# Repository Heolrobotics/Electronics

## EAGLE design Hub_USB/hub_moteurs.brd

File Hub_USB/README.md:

# Hub USB

 **This work is licensed under a [Creative Commons Attribution-ShareAlike 4.0 International License](http://creativecommons.org/licenses/by-sa/4.0/).**

**Authors:** Alexandre Le Falher, Nicolas.

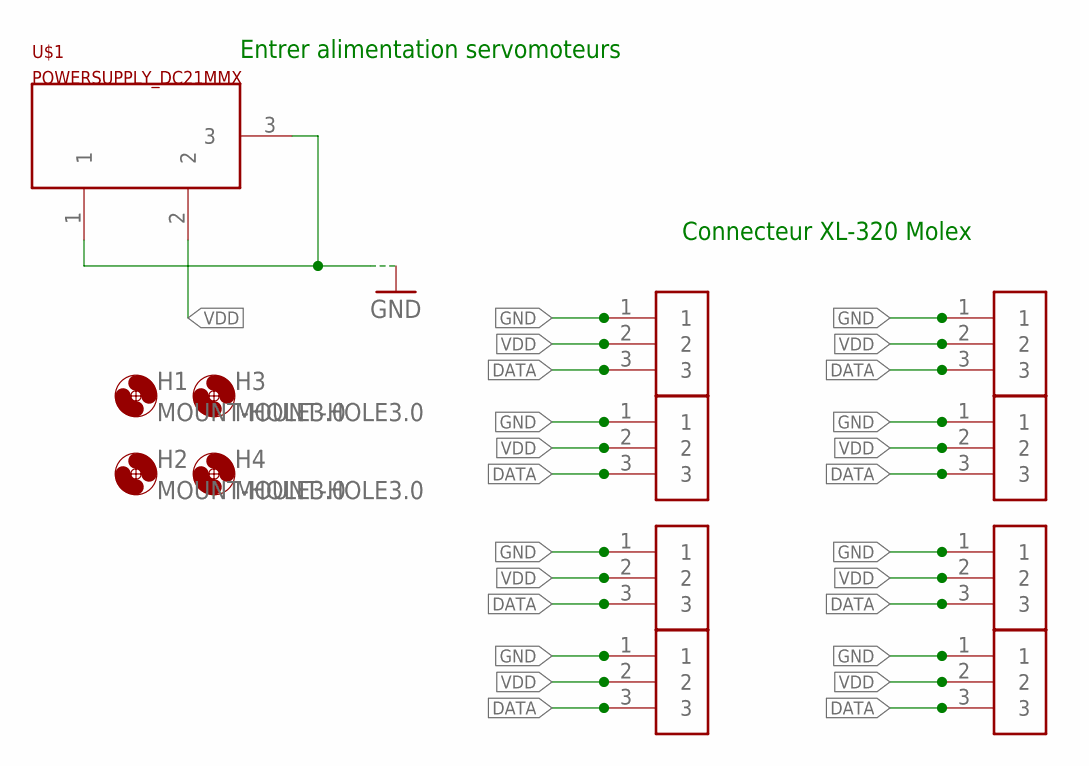
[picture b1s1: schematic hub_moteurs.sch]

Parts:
H1, H2, H3, H4: MOUNT-HOLE3.0; 3,0
U$1: POWERSUPPLY_DC21MMX; POWERSUPPLY_DC-21MM
U$2, U$3, U$4, U$5, U$6, U$7, U$8, U$9: CON_XL-320

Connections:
DATA: U$2.3, U$3.3, U$4.3, U$5.3, U$6.3, U$7.3, U$8.3, U$9.3
GND: U$1.1, U$1.3, U$2.1, U$3.1, U$4.1, U$5.1, U$6.1, U$7.1, U$8.1, U$9.1
VDD: U$1.2, U$2.2, U$3.2, U$4.2, U$5.2, U$6.2, U$7.2, U$8.2, U$9.2

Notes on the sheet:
Connecteur XL-320 Molex
Entrer alimentation servomoteurs

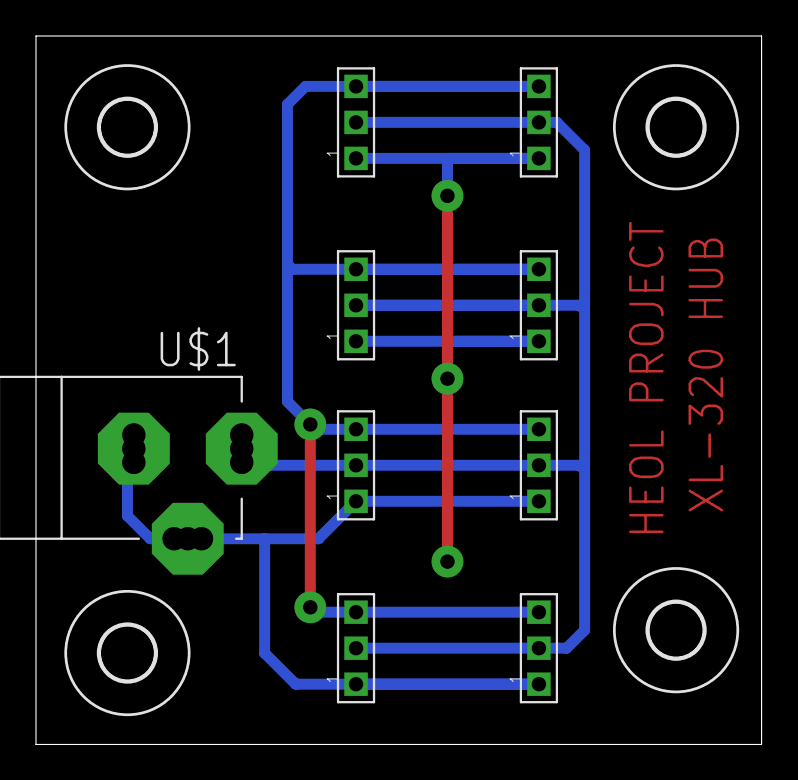
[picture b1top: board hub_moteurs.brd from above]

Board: 2 copper layers, 40.3 x 39.4 mm, 13 parts (0 on the bottom side), 3 nets.
